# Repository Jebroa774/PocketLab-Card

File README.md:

# PocketLab Card V1

PocketLab Card V1 is an original, credit-card-outline ESP32-S3 field tool with
Wi-Fi/BLE control, NFC, LF RFID, Sub-GHz, infrared, removable storage and a
small local user interface. The hardware is designed around a four-layer PCB,
a single-cell LiPo supply and parts that can be assembled by JLCPCB or fitted by
hand where practical.

> [!NOTE]
> **Proudly vibe-coded.** The project grows through hands-on experimentation,
> rapid idea-driven iteration and AI-assisted engineering. Here, vibe coding
> does not mean blindly trusting generated output: the hardware remains an
> engineering prototype until its schematic, PCB, DRC/DFM results and physical
> measurements have been independently checked.

> [!WARNING]
> **Engineering prototype — not ready to order.** Placement and electrical
> connectivity are complete: the current routing checkpoint has 0 open
> connection items. It still has 1,164 DRC findings in the saved median run,
> so DRC/DFM cleanup, RF/LF tuning, sourcing review and prototype measurements
> remain required before fabrication.

## Current hardware

| Area | V1 implementation |
|---|---|
| Controller | ESP32-S3-WROOM-1-N8R2 with native USB, Wi-Fi and BLE |
| 13.56 MHz NFC | PN532 with a project-local 35 x 27 mm four-turn PCB antenna |
| 125 kHz LF RFID | HTRC110 front end with a removable, measurable and tuneable coil |
| Sub-GHz | E07-900MM10S/CC1101 module, tuneable pi network and inboard 868 MHz spring antenna |
| Infrared | Three independent high-power 940 nm emitters plus a 38 kHz receiver |
| Storage and security | microSD, ATECC608C secure element and physical PAIR button |
| User interface | Four RGB LEDs, UP/SELECT/DOWN controls and a firmware-configurable AUX button |
| Sensors | Optional 6-axis IMU, barometer, RTC, fuel gauge and board-temperature monitor |
| Power | USB-C, 1-cell LiPo input, charging/power path, regulated 3.3 V and switchable 5 V |
| Expansion | Protected 2.54 mm breakout matrix with eleven direct expansion GPIOs |

The **ESP32-S3 remains the controller for V1**. The newer ESP32-S31 is being
kept as a possible V2 candidate, but its preliminary hardware ecosystem,
larger WROOM module and immature availability do not justify restarting this
layout.

## Current PCB views

The following images were generated from the current KiCad routing checkpoint.
The hand-fitted IR bodies and spring antenna use approximate preview models;
footprints, courtyards and the PCB outline remain the mechanical references.

<table>
  <tr>
    <td align="center"><br><strong>Top</strong></td>
    <td align="center"><br><strong>Bottom</strong></td>
  </tr>
</table>

More layout and enclosure notes are available in the
[design overview](docs/design-overview/README.md).

## Mechanical target

- 85.60 x 53.98 mm credit-card outline with rounded corners
- Four-layer, nominal 1.2 mm FR-4 using the JLC04121H-7628 stack target
- 1 oz outer and 0.5 oz inner copper with ENIG finish
- Components on both sides; approximately 8–9 mm provisional assembled height
- Three inboard edge-facing IR emitters and an inboard spring-antenna pocket
- Compact unpopulated 6 x 5 matrix of 30 holes on 2.54 mm pitch
- Initial bring-up quantity: five assembled prototype boards

This is a credit-card-shaped instrument, not a wallet-thickness card. The final
height and enclosure clearances must be verified against received components.

## Engineering status

| Check | Current result |
|---|---:|
| Schematic symbols | 274 |
| Assigned footprints | 267 |
| Named logical nets | 181 |
| Physical PCB nets | 231 |
| ERC | 0 errors / 0 warnings |
| Placed footprints | 267 / 267 |
| Routed checkpoint | 2843 track segments / 575 vias / 23 zones |
| Remaining connection items | 0 |
| DRC findings (median of three runs) | 1164 |
| Footprint-library comparison findings | 5 |

Completed design work includes the full schematic, mechanical placement,
four-layer stack definition, native USB pair, local converter routes, RTC
crystal routes, the provisional Sub-GHz feed/pi network and the via-free
back-side LF RFID analog island. All logical connection items are now closed;
the active work is reducing the remaining clearance, hole-clearance, short,
crossing, solder-mask and board-edge DRC findings.

### Before the first PCB order

- Confirm the live JLCPCB stack and recalculate USB/Sub-GHz geometry.
- Review the completed LF/NFC and digital routing against the schematic.
- Finish DRC cleanup, ground stitching and plane review.
- Re-run final KiCad DRC/parity checks from a clean checkout.
- Review every footprint, BOM and placement entry against current supplier data.
- Reconfirm PN532 availability because the part is NRND, and qualify an
  alternative before any production revision.
- Inspect the JLCPCB DFM, BOM and CPL previews and obtain an independent review.
- Tune NFC, LF RFID and Sub-GHz on the assembled prototypes with suitable test
  equipment before treating any RF values as production-ready.

The detailed hand-off state is maintained in the
[work checkpoint](docs/work-checkpoint.md).

## Repository layout

```text
PocketLab-Card/
|-- docs/           Architecture, constraints, checkpoints and current renders
|-- hardware/       KiCad source, local libraries, reports and layout helpers
|-- firmware/       ESP32-S3 firmware source and board configuration
`-- manufacturing/  Fabrication/assembly generation tools and future releases
```

Open `hardware/PocketLab-Card.kicad_pro` in KiCad 10 for the complete project.
The tracked `hardware/PocketLab-Card.kicad_pcb` is the current routing-in-progress
board, not a fabrication release.

## Responsible use

RF, RFID/NFC and infrared functions are intended only for devices, systems,
frequencies, antennas, output levels and duty cycles the operator is legally
permitted to use. Prototype RF performance, electromagnetic compatibility and
regulatory compliance have not yet been verified.

The project is original and does not copy SGP branding, artwork, PCB layout or
firmware.

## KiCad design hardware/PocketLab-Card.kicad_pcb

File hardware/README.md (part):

# Hardware design source

## Functional blocks

| Logical block | Contents |
|---|---|
| 00_ROOT | Power domains, buses and hierarchical connections |
| 01_USB_POWER | USB-C, ESD, charger, battery, 3.3 V and 5 V conversion |
| 02_MCU | ESP32-S3-WROOM-1 module, boot/reset and native USB |
| 03_NFC | PN532, clock, matching/RX networks and four-turn PCB loop |
| 04_SUBGHZ | E07-900MM10S CC1101 module, tuneable pi network and inboard spring antenna |
| 05_LF_RFID_SD | HTRC110, removable 125 kHz coil, level shifting, ATECC608C, PAIR and microSD |
| 06_IR_UI | IR transmitter/receiver, RGB LEDs and buttons |
| 07_SENSORS_IO | IMU, barometer, RTC, fuel gauge, U9/U18 and headers |

KiCad 10 is installed locally. `PocketLab-Card.kicad_pro` is the project entry
point and the PCB scaffold contains the exact credit-card outline. The current
generated schematic comprises 267 symbols and 176 named logical nets; the
OLED-free PCB candidate contains 260 footprints. `reports/erc-nooled-aux.rpt` reports zero
errors and zero warnings.

The schematic and its machine-readable net description are reproducible with
KiCad's bundled Python:

```powershell
& "$env:LOCALAPPDATA\Programs\KiCad\10.0\bin\python.exe" scripts/generate_schematic.py PocketLab-Card.kicad_sch --design-json design-netlist.json
```

The project-local footprint library includes the manufacturer-derived special
packages and `NFC_Loop_35x27mm_4T_TUNE`. The latter is a four-turn, 0.50/0.50
mm preliminary loop with a 35 x 27 mm copper envelope and a full 36 x 29 mm
all-copper-layer keep-out. Its matching is intentionally not a release value:
measure and tune the populated prototype with the final stack-up, enclosure and
battery using a VNA or suitable NFC fixture.

The tracked `PocketLab-Card.kicad_pcb` remains the authoritative design source.
`PocketLab-Card-routing-working.kicad_pcb` is the explicitly named active routing
checkpoint and is kept only so the verified zero-open state can be resumed without
promoting it prematurely. Other generated placement, plane, autorouter and
routing-progress boards are deliberately not versioned because the scripts below
recreate them from the schematic, mechanical template and current rules.

The current PCB contains the guarded digital autorouter fanout plus reviewed local U6/L6,
U7/L7, converter input/output, U7-feedback, RTC-crystal and complete native USB
data routes; L2 remains the uninterrupted ground plane and L3 retains the
power polygons plus explicitly reviewed low-speed signal crossings. R201/R202 are vertical side-by-side 0805
parts, the MCU-side pair stays via-free, and a staggered five-via bridge joins
J1's alternating A/B data pads. U16 is 0.55 mm farther inboard; front-side
0805 R102 now has its J1-B5 pull-down and local ground return routed. The CC2
protection branch to U16 pin 6 is also complete using two ordinary 0.50/0.30-mm
through vias and outer-layer tracks only. SW3/SW7/SW4 are compact, adjacent UP/OK/DOWN
controls; SELECT uses U9/P07 and the BMP390 remains available by I2C polling.
VSYS is now complete through the charger/converter island; an 0805 zero-ohm
SPI_MOSI crossover preserves the plane-only inner layers. Both J1 VBUS contacts
also reach F1 through reviewed local neckdowns and 0.50/0.60-mm B.Cu copper.
The provisional 868-MHz feed now runs through the correctly oriented pi network
and makes its sole signal-layer transition before the spring pocket; its F.Cu
section remains on the narrow PCB bridge outside the notch. The present
checkpoint has 1889 track segments, 343 vias and 23 zones. Both `+5V_RAW` and
`+5V_AUX` are complete on narrow L3 corridors, the requested 36 dense-plane
clusters are closed, and the reviewed U2.3 GND escape is routed. R405 is
oriented with pad 1 toward U3 and pad 2 toward the antenna. The microSD socket
is now 0.175 mm farther inboard, eliminating its ten copper-to-edge findings.
J5.25 now reaches the complete U25/R732 `SPI_SCK_HDR` protection tree through
a reviewed short L3 crossing. J5.23 reaches U24.1 on `I2C_SDA_HDR`; its separate
R730 branch remains in the ratsnest. A single reviewed `+5V_RAW` stitch via
keeps the power polygon connected around the SCK clearance slot, and L2 remains
ground-only.
The short PN532 `/NFC_TX2_F` matching branch from L302.2 to C309.1 is now
routed via-free on F.Cu through the reviewed 0.25-mm local corridor.
The microSD controller-side `/SD_CS_DEV` leg now reaches J2.2 through one local
via; the adjacent U19.2 GND escape was shifted toward the card edge without
changing its reviewed plane via.
The ESP32 `/SPI_MOSI` pad U1.19 now reaches the existing U21/R129 shared-bus
trunk through eight locked outer-layer segments and one 0.45/0.20-mm via.
R511.1 now joins that same trunk through six locked 0.15-mm L3 segments, one
short F.Cu escape and one 0.45/0.20-mm via. The route preserves the continuous
L2 ground plane and the connectivity of both protected L3 5-V polygons.
The USB-C `/USB_CC1` receptacle pad J1.A5 now reaches its back-side 5.1-kohm
pull-down R101 through one outer-layer transition. U16.4 now joins that same
group through nine locked 0.20-mm F.Cu segments, so the complete CC1 detection
and ESD branch is connected without another via.
The UP-button `/USER_BUTTON_A_N` contact SW3.1 now reaches pull-up R608.1
through one short reviewed L3 crossing and two 0.45/0.20-mm vias; U18.11
remains the explicit second group on that net.
The back-side `/CELL_POS` monitor input U8.3 now reaches local capacitor C120.1
through four short, via-free 0.15-mm B.Cu segments.
The back-side `/CELL_POS` sense input R104.1 now joins the charger/battery
branch through three locked 0.20-mm B.Cu segments, one 0.45/0.20-mm tented via
and five locked 0.20-mm F.Cu segments. The route uses the narrow reviewed gap
between C101 and C117 without cutting any inner-layer power polygon.
The protected `/GPIO43` output R718.2 now reaches expansion-header pad J5.11
through three locked 0.15-mm L3 segments and one 0.45/0.20-mm tented via.
The protected `/SPI_MISO_HDR` branch now joins resistor R734.2 to J5 ESD-array
channel U25.1 through eleven locked 0.15-mm segments, two 0.45/0.20-mm tented
vias and a reviewed L3 corridor; the dedicated L2 GND plane remains untouched.
The PN532 `/NFC_TX1` driver pad U2.4 now reaches matching inductor L301.1
through two short F.Cu escapes, three locked 0.20-mm L3 segments and two
0.45/0.20-mm tented vias. Small reviewed jogs in the neighboring LF clock/data
fanouts preserve their connectivity and keep the dedicated L2 GND plane clean.
The active routing checkpoint contains 2843 track segments, 575 ordinary through
vias and 23 zones. Three fresh KiCad DRC runs report zero open connections and
totals between 1162 and 1166 remaining violations (median 1164). The latest cleanup
reroutes EX4, EX5, CHG_TS_FIXED, GPIO8_MCU and SD_DETECT_N, reassigns CHARGER_CHG_N,
and rehomes the AUX5_FAULT_N and BAT_SENSE vias while preserving connectivity.
The earlier cleanup merges one
redundant same-net NFC_OSCOUT via pair, rehomes two crowded GND vias and eliminates
the remaining hole-to-hole findings (three to zero). A CHG_TS L3 detour reduces the
copper-to-edge findings from five to four. Small conventional-through-via rehomes
also improve CHG_ITERM, NFC_DVDD and IR_TX while preserving the long IR_TX inner
trace; no blind or microvias were introduced. The earlier cleanup removes the PWR
copper sliver and both GPIO8-to-rounded-corner edge findings without introducing a
keepout violation. It also merges redundant BAT_SENSE, NFC_SVDD and SD_SCK via
pairs and makes the local USB_CONN_P join via-free.
The remaining violations still require grouped cleanup; the board is therefore not
an order-ready fabrication release.
The matching machine-readable report is `reports/PocketLab-Card-drc.json`.

The latest PN532 cleanup connects U2.5/U2.8 with a short via-free DVDD escape
and replaces the old west-side U2.3 GND detour with a direct exposed-pad
connection. `scripts/route_nfc_dvdd_escape.py` reproduces that reviewed stage.

The LF_RFID_EN branch now reaches U22.1 through a reviewed L3 signal corridor.
The change reuses the former redundant +3V3 via site, reconnects R109 to the
retained +3V3 fanout and leaves L2 as a ground-only plane.
`scripts/route_lf_enable.py` reproduces and connectivity-checks this stage.

The dense U8/U11 sensor corridor is also reworked. U8 SCL reaches U1.6 through
two standard 0.45/0.20-mm through-vias and a short L3 crossing, while U8 SDA
reaches U11.4 directly on B.Cu. `FG_ALERT_N` and `SPI_MOSI` were rerouted
around the corridor, the local U11 ground branches were restored, and L2
remains ground-only. `scripts/route_i2c_sensor_corridor.py` reproduces and
connectivity-checks all six affected endpoint pairs.

The reproducible routing helpers are:

```powershell
# Regenerate the placement and inner-plane staging boards
& "$env:LOCALAPPDATA\Programs\KiCad\10.0\bin\python.exe" scripts/build_pcb.py
& "$env:LOCALAPPDATA\Programs\KiCad\10.0\bin\python.exe" scripts/add_planes.py

# Export the full routing DSN
& "$env:LOCALAPPDATA\Programs\KiCad\10.0\bin\python.exe" scripts/route_pcb.py --export-only --force

# After a reviewed FreeRouting import, apply the local critical-route checkpoint
& "$env:LOCALAPPDATA\Programs\KiCad\10.0\bin\python.exe" scripts/route_critical.py --force

# Reproduce the reviewed LF_RFID_EN endpoint stage on a candidate board
& "$env:LOCALAPPDATA\Programs\KiCad\10.0\bin\python.exe" scripts/route_lf_enable.py --input PocketLab-Card.kicad_pcb --output PocketLab-Card-lf-enable-candidate.kicad_pcb --force

# Reproduce the reviewed U8/U11 I2C sensor corridor on a candidate board
& "$env:LOCALAPPDATA\Programs\KiCad\10.0\bin\python.exe" scripts/route_i2c_sensor_corridor.py --input PocketLab-Card.kicad_pcb --output PocketLab-Card-i2c-sensor-candidate.kicad_pcb --force

# Reproduce the reviewed via-free PN532 TX2 matching branch
& "$env:LOCALAPPDATA\Programs\KiCad\10.0\bin\python.exe" scripts/route_nfc_tx2_matching.py --input PocketLab-Card.kicad_pcb --output PocketLab-Card-nfc-tx2-matching-candidate.kicad_pcb --force

# Reproduce the reviewed microSD CS socket leg and local U19 GND rehome
& "$env:LOCALAPPDATA\Programs\KiCad\10.0\bin\python.exe" scripts/route_sd_cs_socket.py --input PocketLab-Card.kicad_pcb --output PocketLab-Card-sd-cs-candidate.kicad_pcb --force

# Reproduce the reviewed ESP32-to-shared-trunk SPI-MOSI branch
& "$env:LOCALAPPDATA\Programs\KiCad\10.0\bin\python.exe" scripts/route_spi_mosi_mcu.py --input PocketLab-Card.kicad_pcb --output PocketLab-Card-spi-mosi-mcu-candidate.kicad_pcb --force

# Reproduce the reviewed shared-trunk-to-R511 SPI-MOSI branch
& "$env:LOCALAPPDATA\Programs\KiCad\10.0\bin\python.exe" scripts/route_spi_mosi_sd_resistor.py --input PocketLab-Card.kicad_pcb --output PocketLab-Card-spi-mosi-r511-candidate.kicad_pcb --force

# Reproduce the reviewed U8-to-C120 CELL_POS monitor branch
& "$env:LOCALAPPDATA\Programs\KiCad\10.0\bin\python.exe" scripts/route_cell_pos_monitor.py --input PocketLab-Card.kicad_pcb --output PocketLab-Card-cell-pos-monitor-candidate.kicad_pcb --force

# Reproduce the reviewed R104-to-main CELL_POS sense branch
& "$env:LOCALAPPDATA\Programs\KiCad\10.0\bin\python.exe" scripts/route_cell_pos_sense_branch.py --input PocketLab-Card.kicad_pcb --output PocketLab-Card-cell-pos-sense-candidate.kicad_pcb --force

# Reproduce the reviewed protected GPIO43-to-header branch
& "$env:LOCALAPPDATA\Programs\KiCad\10.0\bin\python.exe" scripts/route_gpio43_header.py --input PocketLab-Card.kicad_pcb --output PocketLab-Card-gpio43-header-candidate.kicad_pcb --force

# Reproduce the reviewed protected SPI-MISO resistor-to-ESD branch
& "$env:LOCALAPPDATA\Programs\KiCad\10.0\bin\python.exe" scripts/route_spi_miso_header_esd.py --input PocketLab-Card.kicad_pcb --output PocketLab-Card-spi-miso-header-esd-candidate.kicad_pcb --force

# Reproduce the reviewed PN532 TX1 driver-to-inductor branch
& "$env:LOCALAPPDATA\Programs\KiCad\10.0\bin\python.exe" scripts/route_nfc_tx1_driver.py --input PocketLab-Card.kicad_pcb --output PocketLab-Card-nfc-tx1-candidate.kicad_pcb --force

# Reproduce the reviewed USB-C CC1 receptacle-to-pull-down path
& "$env:LOCALAPPDATA\Programs\KiCad\10.0\bin\python.exe" scripts/route_usb_cc1_resistor.py --input PocketLab-Card.kicad_pcb --output PocketLab-Card-usb-cc1-resistor-candidate.kicad_pcb --force

# Reproduce the reviewed USB-C CC1 receptacle-to-U16 ESD branch
& "$env:LOCALAPPDATA\Programs\KiCad\10.0\bin\python.exe" scripts/route_usb_cc1_esd_branch.py --input PocketLab-Card.kicad_pcb --output PocketLab-Card-usb-cc1-esd-candidate.kicad_pcb --force

# Reproduce the reviewed UP-button contact-to-pull-up path
& "$env:LOCALAPPDATA\Programs\KiCad\10.0\bin\python.exe" scripts/route_user_button_a_pullup.py --input PocketLab-Card.kicad_pcb --output PocketLab-Card-user-button-a-candidate.kicad_pcb --force

# Reproduce the reviewed J5 SDA/SCK protection checkpoint as a candidate chain
& "$env:LOCALAPPDATA\Programs\KiCad\10.0\bin\python.exe" scripts/route_header_bus_protection.py --input PocketLab-Card.kicad_pcb --output PocketLab-Card-header-protection-candidate.kicad_pcb --force
& "$env:LOCALAPPDATA\Programs\KiCad\10.0\bin\python.exe" scripts/rehome_header_neck_fanouts.py --input PocketLab-Card-header-protection-candidate.kicad_pcb --output PocketLab-Card-header-neck-candidate.kicad_pcb --force
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
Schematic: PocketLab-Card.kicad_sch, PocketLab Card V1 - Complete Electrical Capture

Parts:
A1: T3-868M SPRING ANTENNA; T3-868M_Edge_Solder; MPN T3-868M; LCSC C381193
AE1: PCB NFC LOOP - TUNE ON V1; NFC_Loop_35x27mm_4T_TUNE
C101: 4.7nF 1kV; C_0805_2012Metric; MPN C0805C472KDRAC7800; LCSC C5565742
C102, C106, C107, C118, C120, C121, C122, C203, C301, C304, C305, C401, C510, C601, C603, C604, C605, C606, C701, C702, C703, C704, C705, C706, C707: 100nF; C_0402_1005Metric; MPN CL05B104KO5NNNC; LCSC C1525
C103, C105: 4.7uF 10V; C_0603_1608Metric; MPN CL10A475KO8NNNC; LCSC C19666
C104: 22uF 10V; C_0805_2012Metric; MPN TCC0805X5R226K100FT; LCSC C380336
C108, C114, C117, C119: 10uF; C_0805_2012Metric; MPN CL21A106KAYNNNE; LCSC C15850
C109: 10uF DNP - populate only after VSYS stability test; C_0805_2012Metric; MPN CL21A106KAYNNNE; LCSC C15850; not fitted
C110, C111, C112, C115, C116: 22uF; C_0805_2012Metric; MPN TCC0805X5R226K100FT; LCSC C380336
C113, C308, C309: 220pF C0G; C_0603_1608Metric; MPN CL10C221JB8NNNC; LCSC C27675
C123, C124: 10uF 25V X5R HF; C_0805_2012Metric; MPN CL21A106KAYNNNE; LCSC C15850
C201: 1uF; C_0402_1005Metric; MPN CL05A105KA5NQNC; LCSC C52923
C202, C511: 10uF; C_0603_1608Metric; MPN CL10A106KP8NNNC; LCSC C19702
C302: 100nF AVDD; C_0402_1005Metric; MPN CL05B104KO5NNNC; LCSC C1525
C303: 4.7uF VBAT bulk; C_0603_1608Metric; MPN CL10A475KO8NNNC; LCSC C19666
C306, C307: 22pF C0G; C_0603_1608Metric; MPN CL10C220JB8NNNC; LCSC C1653
C310, C311, C312: DNP MATCH; C_0603_1608Metric; not fitted
C313: 10uF DVDD bulk; C_0603_1608Metric; MPN CL10A106KP8NNNC; LCSC C19702
C314: 100nF TVDD; C_0402_1005Metric; MPN CL05B104KO5NNNC; LCSC C1525
C315: 4.7uF TVDD bulk; C_0603_1608Metric; MPN CL10A475KO8NNNC; LCSC C19666
C316: 100nF PVDD; C_0402_1005Metric; MPN CL05B104KO5NNNC; LCSC C1525
C317: 100nF VBAT; C_0402_1005Metric; MPN CL05B104KO5NNNC; LCSC C1525
C318: 1nF C0G RX COUPLING; C_0603_1608Metric; MPN CL10C102JB8NNNC; LCSC C163508
C402, C602: 4.7uF; C_0603_1608Metric; MPN CL10A475KO8NNNC; LCSC C19666
C403, C404: DNP SUBGHZ MATCH; C_0603_1608Metric; not fitted
C501: 100nF HTRC supply; C_0402_1005Metric; MPN CL05B104KO5NNNC; LCSC C1525
C502: 10uF HTRC pulse reservoir; C_0805_2012Metric; MPN CL21A106KAYNNNE; LCSC C15850
C503: 100nF CEXT; C_0402_1005Metric; MPN CL05B104KO5NNNC; LCSC C1525
C504: 100nF QGND; C_0402_1005Metric; MPN CL05B104KO5NNNC; LCSC C1525
C505: 100nF C0G COIL ISOLATION; C_1206_3216Metric; MPN 1206CG104J500NT; LCSC C46348
C506: 3.9nF C0G LF RESONANCE; C_0805_2012Metric; MPN CL21C392JBFNNNE; LCSC C307553
C507: 100pF C0G DNP LF TUNE; C_0603_1608Metric; MPN CL10C101JB8NNNC; LCSC C14858; not fitted
C508: 220pF C0G DNP LF TUNE; C_0603_1608Metric; MPN CL10C221JB8NNNC; LCSC C27675; not fitted
C509: 10pF C0G DNP RX EMI; C_0603_1608Metric; MPN CL10C100JB8NNNC; LCSC C1634; not fitted
C512: 47uF 6.3V LOW-ESR; C_1206_3216Metric; MPN CC1206MKX5R5BB476; LCSC C110047
C513: 100nF OSC supply; C_0402_1005Metric; MPN CL05B104KO5NNNC; LCSC C1525
C515: 100nF LV-AT supply; C_0402_1005Metric; MPN CL05B104KO5NNNC; LCSC C1525
C516: 100nF LVC supply; C_0402_1005Metric; MPN CL05B104KO5NNNC; LCSC C1525
C517: 100nF secure element; C_0402_1005Metric; MPN CL05B104KO5NNNC; LCSC C1525
C607, C617: 22uF 10V X5R IR BUFFER; C_1206_3216Metric; MPN TCC1206X5R226K100HT; LCSC C7393980
C608: 100nF IR HF; C_0402_1005Metric; MPN CL05B104KO5NNNC; LCSC C1525
C609: 100nF X7R; C_0402_1005Metric; MPN CL05B104KO5NNNC; LCSC C1525
D1, D2, D3: VSMY14940 940nm side-view; LED_Vishay_VSMY14940_SideView; MPN VSMY14940; LCSC C511069
D101: SMF5.0A; D_SOD-123F; MPN SMF5.0A; LCSC C151296
F1: Littelfuse 1206L075/13.2; Fuse_1206_3216Metric; MPN 1206L075/13.2WR; LCSC C207036
J1: USB-C DATA/POWER; USB_C_Receptacle_HRO_TYPE-C-31-M-12; MPN TYPE-C-31-M-12; LCSC C165948
J2: microSD; microSD_HC_Molex_104031-0811; MPN 104031-0811; LCSC C585350
J3: EXTERNAL 400uH LF COIL; PinHeader_1x02_P2.54mm_Vertical
J4: PROTECTED 1S LiPo 3.7V; JST_PH_S2B-PH-SM4-TB_1x02-1MP_P2.00mm_Horizontal; MPN S2B-PH-SM4-TB(LF)(SN); LCSC C295747
J5: 30-PIN 2.54mm DUPONT GRID; Dupont_Grid_6x5_P2.54mm
L6: 1.5uH 5.2A SMHT4020; ShunXiangNuo_SMHT4020; MPN SMHT4020-1R5MT; LCSC C46469583
L7: 1uH 4.15A SLW4030S; Sunltech_SLW4030S; MPN SLW4030S1R0NST; LCSC C206354
L301, L302: 560nH C0G/Q; L_0805_2012Metric; MPN FHW0805UFR56JST; LCSC C304279
LED1, LED2, LED3, LED4: WS2812B-2020; LED_WS2812B-2020_PLCC4_2.0x2.0mm; MPN WS2812B-2020; LCSC C965555
Q1: AO3400A IR DRIVER; SOT-23; MPN AO3400A; LCSC C20917
Q2: CSD16406Q3 DISCHARGE; CSD16406Q3_VSON-8_3.3x3.3mm_P0.65mm_JLC; MPN CSD16406Q3; LCSC C2861720
Q3: CSD16406Q3 CHARGE; CSD16406Q3_VSON-8_3.3x3.3mm_P0.65mm_JLC; MPN CSD16406Q3; LCSC C2861720
R101, R102: 5.1k 1%; R_0402_1005Metric; MPN 0402WGF5101TCE; LCSC C25905
R103: 1M; R_0402_1005Metric; MPN 0402WGF1004TCE; LCSC C26083
R104: 330R; R_0402_1005Metric; MPN 0402WGF3300TCE; LCSC C25104
R105: 2.2k; R_0805_2012Metric; MPN 0805W8F2201T5E; LCSC C17520
R106, R107: 5.1M; R_0402_1005Metric; MPN 0402WGF5104TCE; LCSC C270595
R108: 10k TS fixed; R_0805_2012Metric; MPN 0805W8F1002T5E; LCSC C17414
R109, R110, R115, R122, R124, R126, R127, R128, R603: 100k; R_0402_1005Metric; MPN 0402WGF1003TCE; LCSC C25741
R111: 3.48k 1%; R_0402_1005Metric; MPN 0402WGF3481TCE; LCSC C22065
R112: 3.01k 1%; R_0402_1005Metric; MPN 0402WGF3011TCE; LCSC C25889
R113: 1.78k 1%; R_0402_1005Metric; MPN 0402WGF1781TCE; LCSC C113478
R114: 68.1k 1%; R_0402_1005Metric; MPN 0402WGF6812TCE; LCSC C11537
R116, R125, R203, R204, R301, R519, R607, R608, R609, R703: 10k; R_0402_1005Metric; MPN 0402WGF1002TCE; LCSC C25744
R117: 470k 1%; R_0402_1005Metric; MPN 0402WGF4703TCE; LCSC C25790
R118: 150k 1%; R_0402_1005Metric; MPN 0402WGF1503TCE; LCSC C25755
R119: 10k; R_0805_2012Metric; MPN 0805W8F1002T5E; LCSC C17414
R120: 732k 1%; R_0402_1005Metric; MPN 0402WGF7323TCE; LCSC C27016
R121: 100k 1%; R_0402_1005Metric; MPN 0402WGF1003TCE; LCSC C25741
R123: 60.4k 1%; R_0402_1005Metric; MPN 0402WGF6042TCE; LCSC C25911
R129: 0R SPI CROSSOVER; R_0805_2012Metric; MPN 0805W8F0000T5E; LCSC C17477
R201, R202: 22R; R_0805_2012Metric; MPN 0805W8F220JT5E; LCSC C17561
R302: 10k RESET default asserted; R_0402_1005Metric; MPN 0402WGF1002TCE; LCSC C25744
R303, R304: 0R MATCH; R_0603_1608Metric; MPN 0603WAF0000T5E; LCSC C21189
R305: 2.7k RX TAP; R_0603_1608Metric; MPN 0603WAF2701T5E; LCSC C13167
R306: 1k VMID BIAS; R_0603_1608Metric; MPN 0603WAF1001T5E; LCSC C21190
R401, R402, R403, R404, R510, R511, R512, R513: 22R; R_0402_1005Metric; MPN 0402WGF220JTCE; LCSC C25092
R405: 0R SUBGHZ MATCH; R_0603_1608Metric; MPN 0603WAF0000T5E; LCSC C21189
R406: 100k CS SAFE-HIGH; R_0402_1005Metric; MPN 0402WGF1003TCE; LCSC C25741
R501: 100R QOD discharge; R_0402_1005Metric; MPN 0402WGF1000TCE; LCSC C25076
R502: 47R 0.5W ANTENNA CURRENT LIMIT; R_1210_3225Metric; MPN 1210W2F470JT5E; LCSC C474213
R503: 1k LF EMI RETURN; R_0402_1005Metric; MPN 0402WGF1001TCE; LCSC C11702
R504: 150k 1% RX DIVIDER; R_0402_1005Metric; MPN 0402WGF1503TCE; LCSC C25755
R506: 100k SAFE-OFF; R_0402_1005Metric; MPN 0402WGF1003TCE; LCSC C25741
R509: 10k PAIR pull-up; R_0402_1005Metric; MPN 0402WGF1002TCE; LCSC C25744
R514, R515, R516, R517, R518: 47k; R_0402_1005Metric; MPN 0402WGF4702TCE; LCSC C25792
R601, R610, R611: 68R 0.25W anti-surge; R_0603_1608Metric; MPN AS03W4J0680T5E; LCSC C966162
R602, R604, R710, R711, R712, R713, R715, R716, R717, R718, R719, R720, R721, R730, R731, R732, R733, R734: 100R; R_0402_1005Metric; MPN 0402WGF1000TCE; LCSC C25076
R605: 68R; R_0402_1005Metric; MPN 0402WGF680JTCE; LCSC C25131
R606: 100R PAIR GPIO PROTECTION; R_0402_1005Metric; MPN 0402WGF1000TCE; LCSC C25076
R701: 3.3k; R_0805_2012Metric; MPN 0805W8F3301T5E; LCSC C26010
R702: 3.3k; R_0402_1005Metric; MPN 0402WGF3301TCE; LCSC C25890
R714: 100R BOARD TEMP PROBE; R_0402_1005Metric; MPN 0402WGF1000TCE; LCSC C25076
R722, R723, R724, R725, R726, R727, R728, R729: 220R EXPANSION PROTECTION; R_0402_1005Metric; MPN 0402WGF2200TCE; LCSC C25091
R735: 100k EN pull-down; R_0805_2012Metric; MPN 0805W8F1003T5E; LCSC C149504
R736: 10k 1% BOARD TEMP BIAS; R_0402_1005Metric; MPN 0402WGF1002TCE; LCSC C25744
RT701: 10k NTC B3950 1%; R_0603_1608Metric; MPN KNTC0603/10KF3950; LCSC C2892547
SJ1: TS FIXED / CUT FOR EXT NTC; SolderJumper-2_P1.3mm_Bridged_RoundedPad1.0x1.5mm
SW1: RESET; SW_HYP_1TS015A_3.0x2.0mm; MPN 1TS015A-1600-0600-CT; LCSC C256104
SW2: BOOT; SW_HYP_1TS015A_3.0x2.0mm; MPN 1TS015A-1600-0600-CT; LCSC C256104
SW3: UP; SW_HYP_1TS015A_3.0x2.0mm; MPN 1TS015A-1600-0600-CT; LCSC C256104
SW4: DOWN; SW_HYP_1TS015A_3.0x2.0mm; MPN 1TS015A-1600-0600-CT; LCSC C256104
SW5: MAIN POWER OFF / ON; SW_SPDT_Shouhan_MSK12C02; MPN MSK12C02; LCSC C431540
SW6: PAIR; SW_HYP_1TS015A_3.0x2.0mm; MPN 1TS015A-1600-0600-CT; LCSC C256104
SW7: SELECT; SW_HYP_1TS015A_3.0x2.0mm; MPN 1TS015A-1600-0600-CT; LCSC C256104
SW8: AUX CONFIG; SW_SPST_CK_KXT3; MPN KXT311LHS
TP101: BATTERY CELL_POS; TestPoint_Pad_D1.0mm
TP102: BATTERY CELL_NEG; TestPoint_Pad_D1.0mm
TP103: BATTERY BAT_FET_MID; TestPoint_Pad_D1.0mm
TP104: BATTERY GND; TestPoint_Pad_D1.0mm
TP105: POWER VBUS_USB; TestPoint_Pad_D1.0mm
TP106: POWER VBUS_FUSED; TestPoint_Pad_D1.0mm
TP107: POWER VSYS; TestPoint_Pad_D1.0mm
TP108: POWER +3V3; TestPoint_Pad_D1.0mm
TP109: POWER +5V_RAW; TestPoint_Pad_D1.0mm
TP110: POWER +5V_AUX; TestPoint_Pad_D1.0mm
TP201: JTAG_STRAP_TP; TestPoint_Pad_D1.0mm
TP202: STRAP_BOOT_TP; TestPoint_Pad_D1.0mm
TP203: STRAP_VDD_SPI_TP; TestPoint_Pad_D1.0mm
TP301: NFC_LOADMOD TEST; TestPoint_Pad_D1.0mm
TP502: LF ANTENNA TAP - HIGH VOLTAGE; TestPoint_Pad_D1.0mm
U1: ESP32-S3-WROOM-1-N8R2; ESP32-S3-WROOM-1_PhysicalCourtyard; MPN ESP32-S3-WROOM-1-N8R2; LCSC C2913204
U2: PN5321A3HN/C106; HVQFN-40-1EP_6x6mm_P0.5mm_EP4.1x4.1mm; MPN PN5321A3HN/C106; LCSC C880904
U3: E07-900MM10S 855-925MHz; E07-900MM10S; MPN E07-900MM10S; LCSC C5844212
U4: HTRC11001T/03EE,11 125kHz; SO-14_3.9x8.65mm_P1.27mm; MPN HTRC11001T/03EE,11; LCSC C501317
U5: BQ24074RGTR; VQFN-16-1EP_3x3mm_P0.5mm_EP1.6x1.6mm_ThermalVias; MPN BQ24074RGTR; LCSC C54313
U6: TPS63070RNMR 3V3; TPS63070_RNM0015A; MPN TPS63070RNMR; LCSC C109322
U7: TPS61023DRLR 5V BOOST; SOT-563; MPN TPS61023DRLR; LCSC C919459
U8: MAX17048G+T10; TDFN-8-1EP_2x2mm_P0.5mm_EP0.8x1.2mm; MPN MAX17048G+T10; LCSC C2682616
U9: TCA9535PWR; TSSOP-24_4.4x7.8mm_P0.65mm; MPN TCA9535PWR; LCSC C130204
U10: BMI270 (FULL OPTION); Bosch_LGA-14_3x2.5mm_P0.5mm; MPN BMI270; LCSC C2836813
U11: BMP390 (FULL OPTION); BMP390_LGA-10_2x2mm; MPN BMP390; LCSC C5124834
U12: PCF8563T; SOIC-8_3.9x4.9mm_P1.27mm; MPN PCF8563T/5,518; LCSC C7440
U13: TSOP75338WTR 38kHz; TSOP75338WTR_HeimdallW_SideView; MPN TSOP75338WTR; LCSC C7365598
U14: BQ29700DSE; WSON-6_1.5x1.5mm_P0.5mm; MPN BQ29700DSER; LCSC C183096
U15: TPS2553DBVR 500mA LIMIT; SOT-23-6; MPN TPS2553DBVR; LCSC C55266
U16: USBLC6-4SC6Y; SOT-23-6; MPN USBLC6-4SC6Y; LCSC C435848
U17: TPS22919DCKR LF 5V LOAD SWITCH; SOT-363_SC-70-6; MPN TPS22919DCKR; LCSC C2149796
U18: TCA9534PWR INTERNAL CONTROL; TSSOP-16_4.4x5mm_P0.65mm; MPN TCA9534PWR; LCSC C783615
U19: SRV05-4MR6T1G SD ESD; SOT-23-6; MPN SRV05-4MR6T1G; LCSC C604719
U20: SN74AHCT1G126DBVR RGB LEVEL SHIFT; SOT-23-5; MPN SN74AHCT1G126DBVR; LCSC C163712
U21: SN74LV125ATPWR LF/SPI 3V3-TO-5V IOFF; TSSOP-14_4.4x5mm_P0.65mm; MPN SN74LV125ATPWR; LCSC C2675655
U22: SN74LVC1G126DBVR LF 5V-TO-3V3 TRI-STATE; SOT-23-5; MPN SN74LVC1G126DBVR; LCSC C7834
U23: ATECC608C-SSHDA-T; SOIC-8_3.9x4.9mm_P1.27mm; MPN ATECC608C-SSHDA-T; LCSC C28975195
U24: SRV05-4MR6T1G J5 BUS ESD; SOT-23-6; MPN SRV05-4MR6T1G; LCSC C604719
U25: SRV05-4MR6T1G J5 SPI ESD; SOT-23-6; MPN SRV05-4MR6T1G; LCSC C604719
Y301: 27.12MHz crystal (pins 2/4 shield); Crystal_SMD_3225-4Pin_3.2x2.5mm; MPN XXDBBCNANF-27.12M; LCSC C124317
Y501: 4MHz 5V CMOS OSCILLATOR; Oscillator_SMD_EuroQuartz_XO32-4Pin_3.2x2.5mm_RotB; MPN OH2EL89CFI-111YLC-4M; LCSC C42448900
Y701: 32.768kHz CL=7pF; Crystal_SMD_3215-2Pin_3.2x1.5mm; MPN ABS07-32.768KHZ-7-T; LCSC C276424

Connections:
/+3V3: C110.1, C111.1, C112.1, C124.1, C202.1, C203.1, C303.1, C316.1, C317.1, C401.1, C402.1, C510.1, C511.1, C512.1, C516.1, C517.1, C701.1, C702.1, C703.1, C704.1, C705.1, C706.1, C707.1, J2.4 (VDD), J5.1, R109.2, R110.2, R117.1, R119.2, R124.2, R125.2, R203.2, R204.2, R406.2, R509.2, R514.2, R515.2, R516.2, R517.2, R518.2, R519.2, R604.1, R607.2, R608.2, R609.2, R701.2, R702.2, R703.2, R736.1, TP108.1, U1.2 (3V3), U2.23 (PVDD), U2.40 (VBAT), U3.1, U6.7, U6.8, U9.24 (VCC), U10.5, U10.8, U10.12, U11.1, U11.6, U11.10, U12.8 (VDD), U18.1 (A0), U18.16 (VDD), U19.5 (VP), U22.5 (VCC), U23.8 (VCC), U24.5 (VP), U25.5 (VP); also elsewhere on the board
/+5V_AUX: C118.1, C119.1, J5.29, TP110.1, U15.6
/+5V_RAW: C113.1, C115.1, C116.1, C117.1, C603.1, C604.1, C605.1, C606.1, C607.1, C608.1, C609.1, C617.1, LED1.1 (VDD), LED2.1 (VDD), LED3.1 (VDD), LED4.1 (VDD), R120.1, R601.1, R610.1, R611.1, TP109.1, U7.6, U15.1, U17.1, U20.5 (VCC)
/AUX5_EN: R127.1, U15.3, U18.6 (P2)
/AUX5_FAULT_N: R124.1, U9.7 (P03), U15.4
/BAT_COUT: Q3.4, R107.1, U14.2 (Cout)
/BAT_DOUT: Q2.4, R106.1, U14.3 (Dout)
/BAT_FET_MID: Q2.5, Q3.5, TP103.1
/BAT_SENSE: C102.1, R104.2, U14.5 (BAT)
/BAT_VMINUS: R105.1, U14.6 (V-)
/BMI_INT1: U9.9 (P05), U10.4
/BMI_INT2: U9.10 (P06), U10.9
/BOARD_TEMP_ADC: R714.1, R736.2, RT701.1, U1.17 (IO9)
/BOARD_TEMP_HDR: J5.7, R714.2
/BOOST5_EN: R122.1, U7.2, U18.10 (P5), U20.1
/BOOT_N: R204.1, SW2.1, U1.27 (IO0)
/BQ_EN1: R115.1, U5.6 (EN1), U18.4 (P0)
/BQ_EN2: R128.1, U5.5 (EN2)
/CELL_NEG: C102.2, J4.2, Q2.1, Q2.2, Q2.3, R106.2, TP102.1, U14.4 (VSS)
/CELL_POS: C104.1, C120.1, C121.1, J4.1, R104.1, TP101.1, U5.2 (BAT), U5.3 (BAT), U8.3
/CHARGER_CHG_N: R110.1, U5.9 (~CHG), U9.5 (P01)
/CHARGER_PGOOD_N: R109.1, U5.7 (~PGOOD), U9.6 (P02)
/CHG_DISABLE: R126.1, U5.4 (~CE), U18.5 (P1)
/CHG_ILIM: R111.1, U5.12 (ILIM)
/CHG_ISET: R113.1, U5.16 (ISET)
/CHG_ITERM: R112.1, U5.15 (ITERM)
/CHG_TMR: R114.1, U5.14 (TMR)
/CHG_TS: J5.28, SJ1.1 (A), U5.1 (TS)
/CHG_TS_FIXED: R108.1, SJ1.2 (B)
/ESP_EN: C201.1, R203.1, SW1.1, U1.3 (EN); also elsewhere on the board
/EX0: J5.15, R722.2
/EX0_INT: R722.1, U9.13 (P10)
/EX1: J5.16, R723.2
/EX1_INT: R723.1, U9.14 (P11)
/EX2: J5.17, R724.2
/EX2_INT: R724.1, U9.15 (P12)
/EX3: J5.18, R725.2
/EX3_INT: R725.1, U9.16 (P13)
/EX4: J5.19, R726.2
/EX4_INT: R726.1, U9.17 (P14)
/EX5: J5.20, R727.2
/EX5_INT: R727.1, U9.18 (P15)
/EX6: J5.21, R728.2
/EX6_INT: R728.1, U9.19 (P16)
/EX7: J5.22, R729.2
/EX7_INT: R729.1, U9.20 (P17)
/FG_ALERT_N: R125.1, U8.5, U9.8 (P04)
/GND: C101.2, C103.2, C104.2, C105.2, C106.2, C107.2, C108.2, C109.2, C110.2, C111.2, C112.2, C114.2, C115.2, C116.2, C117.2, C118.2, C119.2, C120.2, C121.2, C122.2, C123.2, C124.2, C201.2, C202.2, C203.2, C301.2, C302.2, C303.2, C304.2, C305.2, C306.2, C307.2, C308.2, C309.2, C311.2, C312.2, C313.2, C314.2, C315.2, C316.2, C317.2, C401.2, C402.2, C403.2, C404.2, C501.2, C502.2, C503.2, C504.2, C510.2, C511.2, C512.2, C513.2, C515.2, C516.2, C517.2, C601.2, C602.2, C603.2, C604.2, C605.2, C606.2, C607.2, C608.2, C609.2, C617.2, C701.2, C702.2, C703.2, C704.2, C705.2, C706.2, C707.2, D101.2 (A), J1.A1 (GND), J1.A12 (GND), J1.B1 (GND), J1.B12 (GND), J2.6 (VSS), J2.9 (DET_B), J2.SH (SHIELD), J5.2, J5.30, LED1.3 (VSS), LED2.3 (VSS), LED3.3 (VSS), LED4.3 (VSS), Q1.2 (S), Q3.1, Q3.2, Q3.3, R101.2, R102.2, R103.2, R105.2, R107.2, R108.2, R111.2, R112.2, R113.2, R114.2, R115.2, R118.2, R121.2, R122.2, R123.2, R126.2, R127.2, R128.2, R302.2, R503.2, R506.2, R603.2, R735.2, RT701.2, SW1.2, SW2.2, SW3.2, SW4.2, SW5.1 (A), SW6.2, SW7.2, SW8.2, TP104.1, U1.1 (GND), U1.40 (GND), U1.41 (GND), U2.1 (DVSS), U2.3 (TVSS1), U2.7 (TVSS2), U2.11 (AVSS), U2.17 (I1), U2.18 (TESTEN), U2.41 (AVSS), U3.2, U3.7, U3.16, U4.1 (VSS), U4.5 (MODE), U5.8 (VSS), U5.17 (VSS), U6.4, U6.10, U6.15, U7.4, U8.1, U8.4, U8.6, U8.9, U9.2 (A1), U9.3 (A2), U9.12 (GND), U9.21 (A0), U10.1, U10.6, U10.7, U11.3, U11.5, U11.8, U11.9, U12.4 (VSS), U13.1, U13.4, U15.2, U16.2 (GND), U17.2, U18.2 (A1), U18.3 (A2), U18.8 (GND), U19.2 (VN), U20.3 (GND), U21.1, U21.2, U21.4, U21.7, U21.9, U21.10, U21.13, U22.3 (GND), U23.4 (GND), U24.2 (VN), U25.2 (VN), Y301.2, Y301.4, Y501.2; also elsewhere on the board
/GPIO1: J5.3, R710.2
/GPIO1_MCU: R710.1, U1.39 (IO1)
/GPIO2: J5.4, R711.2
/GPIO2_MCU: R711.1, U1.38 (IO2)
/GPIO4: J5.5, R712.2
/GPIO4_MCU: R712.1, U1.4 (IO4)
/GPIO8: J5.6, R713.2
/GPIO8_MCU: R713.1, U1.12 (IO8)
/GPIO38_MCU: R606.1, U1.31 (IO38)
/GPIO40: J5.8, R715.2
/GPIO40_MCU: R715.1, U1.33 (IO40)
/GPIO41: J5.9, R716.2
/GPIO41_MCU: R716.1, U1.34 (IO41)
/GPIO42: J5.10, R717.2
/GPIO42_MCU: R717.1, U1.35 (IO42)
/GPIO43: J5.11, R718.2
/GPIO43_MCU: R718.1, U1.37 (TXD0)
/GPIO44: J5.12, R719.2
/GPIO44_MCU: R719.1, U1.36 (RXD0)
/GPIO47: J5.13, R720.2
/GPIO47_MCU: R720.1, U1.24 (IO47)
/GPIO48: J5.14, R721.2
/GPIO48_MCU: R721.1, U1.25 (IO48)
/I2C_SCL: R702.1, R731.1, U1.6 (IO6), U2.27 (NSS/P50_SCL/HSU_RX), U8.7, U9.22 (SCL), U10.13, U11.2, U12.6 (SCL), U18.14 (SCL), U23.6 (SCL); also elsewhere on the board
/I2C_SCL_HDR: J5.24, R731.2, U24.3 (IO2)
/I2C_SDA: R701.1, R730.1, U1.5 (IO5), U2.28 (MOSI/SDA/HSU_TX), U8.8, U9.23 (SDA), U10.14, U11.4, U12.5 (SDA), U18.15 (SDA), U23.5 (SDA); also elsewhere on the board
/I2C_SDA_HDR: J5.23, R730.2, U24.1 (IO1)
/IOEXP_INT_N: R703.1, U1.32 (IO39), U9.1 (~INT), U18.13 (~INT)
/IR_GATE: Q1.1 (G), R602.2, R603.1
/IR_LED_A1: D1.2 (A), R601.2
/IR_LED_A2: D2.2 (A), R610.2
/IR_LED_A3: D3.2 (A), R611.2
/IR_LED_K: D1.1 (K), D2.1 (K), D3.1 (K), Q1.3 (D)
/IR_RX: U1.30 (IO37), U13.3
/IR_RX_VS: C601.1, C602.1, R604.2, U13.2
/IR_TX: R602.1, U1.29 (IO36)
/JTAG_STRAP_TP: TP201.1, U1.15 (IO3)
/LF_5V: C501.1, C502.1, C513.1, C515.1, R501.2, U4.3 (VDD), U17.6, U21.14, Y501.1, Y501.4
/LF_ANT_A: C505.2, J3.1, R503.1
/LF_ANT_B: J3.2, R502.1
/LF_CEXT: C503.1, U4.12 (CEXT)
/LF_CLK_4M: U4.6 (XTAL1), Y501.3
/LF_DIN_5V: U4.9 (DIN), U21.11
/LF_DOUT_5V: U4.10 (DOUT), U22.2
/LF_QGND: C504.1, C509.2, U4.13 (QGND)
/LF_QOD: R501.1, U17.5
/LF_RFID_EN: R506.1, U17.3, U18.9 (P4), U22.1
/LF_RX: C509.1, R504.2, U4.14 (RX)
/LF_SCLK_5V: U4.8 (SCLK), U21.6
/LF_TAP: C506.1, C507.1, C508.1, R502.2, R504.1, TP502.1
/LF_TX1: C505.1, U4.4 (TX1)
/LF_TX2: C506.2, C507.2, C508.2, U4.2 (TX2)
/NFC_DVDD: C302.1, C304.1, C313.1, C314.1, C315.1, R301.2, U2.5 (TVDD), U2.8 (AVDD), U2.39 (DVDD)
/NFC_I0: R301.1, U2.16 (I0)
/NFC_IRQ_N: U1.7 (IO7), U2.25 (P70_IRQ)
/NFC_LOADMOD: TP301.1, U2.2 (LOADMOD)
/NFC_LOOP_A: AE1.1, C310.1, C311.1, R303.2, R305.1
/NFC_LOOP_B: AE1.2, C310.2, C312.1, R304.2
/NFC_OSCIN: C306.1, U2.14 (OSCIN), Y301.1
/NFC_OSCOUT: C307.1, U2.15 (OSCOUT), Y301.3
/NFC_RESET_N: R302.1, U2.38 (~RSTPD), U18.7 (P3)
/NFC_RX: C318.2, R306.2, U2.10 (RX)
/NFC_RX_AC: C318.1, R305.2
/NFC_SVDD: C305.1, U2.37 (SVDD)
/NFC_TX1: L301.1, U2.4 (TX1)
/NFC_TX1_F: C308.1, L301.2, R303.1
/NFC_TX2: L302.1, U2.6 (TX2)
/NFC_TX2_F: C309.1, L302.2, R304.1
/NFC_VMID: C301.1, R306.1, U2.9 (VMID)
/PAIR_N: R509.1, R606.2, SW6.1
/PWR_3V3_PG: R119.1, U6.2
/PWR_SW_ON: R116.2, SW5.3 (C)
/RGB_BUF_5V: R605.1, U20.4
/RGB_D1_2: LED1.2 (DOUT), LED2.4 (DIN)
/RGB_D2_3: LED2.2 (DOUT), LED3.4 (DIN)
/RGB_D3_4: LED3.2 (DOUT), LED4.4 (DIN)
/RGB_DATA: U1.18 (IO10), U20.2
/RGB_DIN1: LED1.4 (DIN), R605.2
/RTC_OSCI: U12.1 (OSCI), Y701.1
/RTC_OSCO: U12.2 (OSCO), Y701.2
/SD_CS_DEV: J2.2 (DAT3/CD), R510.2, R515.1, U19.1 (IO1)
/SD_CS_N: R510.1, U1.10 (IO17)
/SD_DAT1: J2.8 (DAT1), R518.1
/SD_DAT2: J2.1 (DAT2), R514.1
/SD_DETECT_N: J2.10 (DET_A), R519.1, U9.4 (P00)
/SD_MISO: J2.7 (DAT0), R513.2, R517.1, U19.6 (IO4)
/SD_MOSI: J2.3 (CMD), R511.2, R516.1, U19.3 (IO2)
/SD_SCK: J2.5 (CLK), R512.2, U19.4 (IO3)
/SPI_MISO: R403.1, R513.1, R734.1, U1.21 (IO13), U22.4
/SPI_MISO_HDR: J5.27, R734.2, U25.1 (IO1)
/SPI_MOSI: R129.2, R511.1, R733.1, U1.19 (IO11), U21.12
/SPI_MOSI_HDR: J5.26, R733.2, U25.3 (IO2)
/SPI_MOSI_JMP: R129.1, R402.1
/SPI_SCK: R401.1, R512.1, R732.1, U1.20 (IO12), U21.5
/SPI_SCK_HDR: J5.25, R732.2, U25.4 (IO3)
/STRAP_BOOT_TP: TP202.1, U1.16 (IO46)
/STRAP_VDD_SPI_TP: TP203.1, U1.26 (IO45)
/SUBGHZ_CS_N: R404.1, U1.22 (IO14)
/SUBGHZ_GDO0: U1.8 (IO15), U3.18
/SUBGHZ_GDO2: U1.9 (IO16), U3.20
/SUBGHZ_RF_ANT: A1.1, C404.1, R405.2
/SUBGHZ_RF_MOD: C403.1, R405.1, U3.6
/SUB_CS_N: R404.2, R406.1, U3.14
/SUB_MISO: R403.2, U3.12
/SUB_MOSI: R402.2, U3.13
/SUB_SCK: R401.2, U3.15
/U6_FB: R117.2, R118.1, U6.5
/U6_L1: L6.1, U6.11
/U6_L2: L6.2, U6.9
/U6_PS_SYNC: R735.1, SW5.2 (B), U6.1, U6.14
/U6_VAUX: C107.1, U6.3
/U7_FB: C113.2, R120.2, R121.1, U7.1
/U7_SW: L7.2, U7.5
/U15_ILIM: R123.1, U15.5
/USB_CC1: J1.A5 (CC1), R101.1, U16.4 (I/O3)
/USB_CC2: J1.B5 (CC2), R102.1, U16.6 (I/O4)
/USB_CONN_N: J1.A7 (D-), J1.B7 (D-), R201.1, U16.3 (I/O2)
/USB_CONN_P: J1.A6 (D+), J1.B6 (D+), R202.1, U16.1 (I/O1)
/USB_D_N: R201.2, U1.13 (USB_D-)
/USB_D_P: R202.2, U1.14 (USB_D+)
/USB_SHIELD: C101.1, J1.SH (SHIELD), R103.1
/USER_BUTTON_A_N: R608.1, SW3.1, U18.11 (P6)
/USER_BUTTON_B_N: R609.1, SW4.1, U18.12 (P7)
/USER_BUTTON_SELECT_N: R607.1, SW7.1, U9.11 (P07)
/VBUS_FUSED: C103.1, C106.1, D101.1 (K), F1.2, TP106.1, U5.13 (IN), U16.5 (VBUS)
/VBUS_USB: F1.1, J1.A4 (VBUS), J1.A9 (VBUS), J1.B4 (VBUS), J1.B9 (VBUS), TP105.1
/VSYS: C105.1, C108.1, C109.1, C114.1, C122.1, C123.1, L7.1, R116.1, TP107.1, U5.10 (OUT), U5.11 (OUT), U6.12, U6.13, U7.3
unnamed: SW8.1, U1.23 (IO21)

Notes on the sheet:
01 USB / BATTERY / POWER
02 ESP32-S3 MCU / USB
03 PN532 NFC / TUNABLE LOOP
04 E07 CC1101 SUB-GHZ
05 LF RFID / SECURITY / MICROSD
06 IR / RGB / BUTTONS
07 SENSORS / RTC / IO EXPANSION

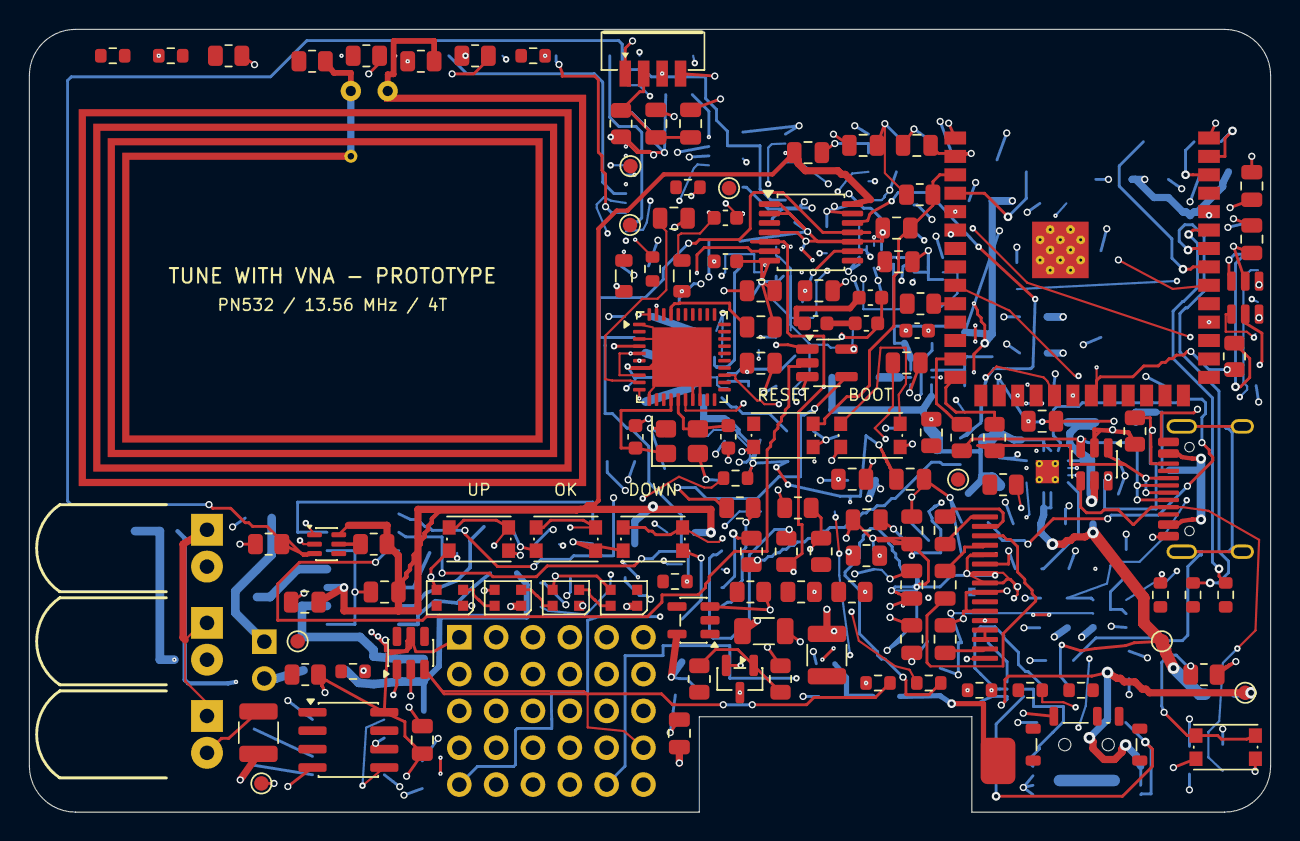
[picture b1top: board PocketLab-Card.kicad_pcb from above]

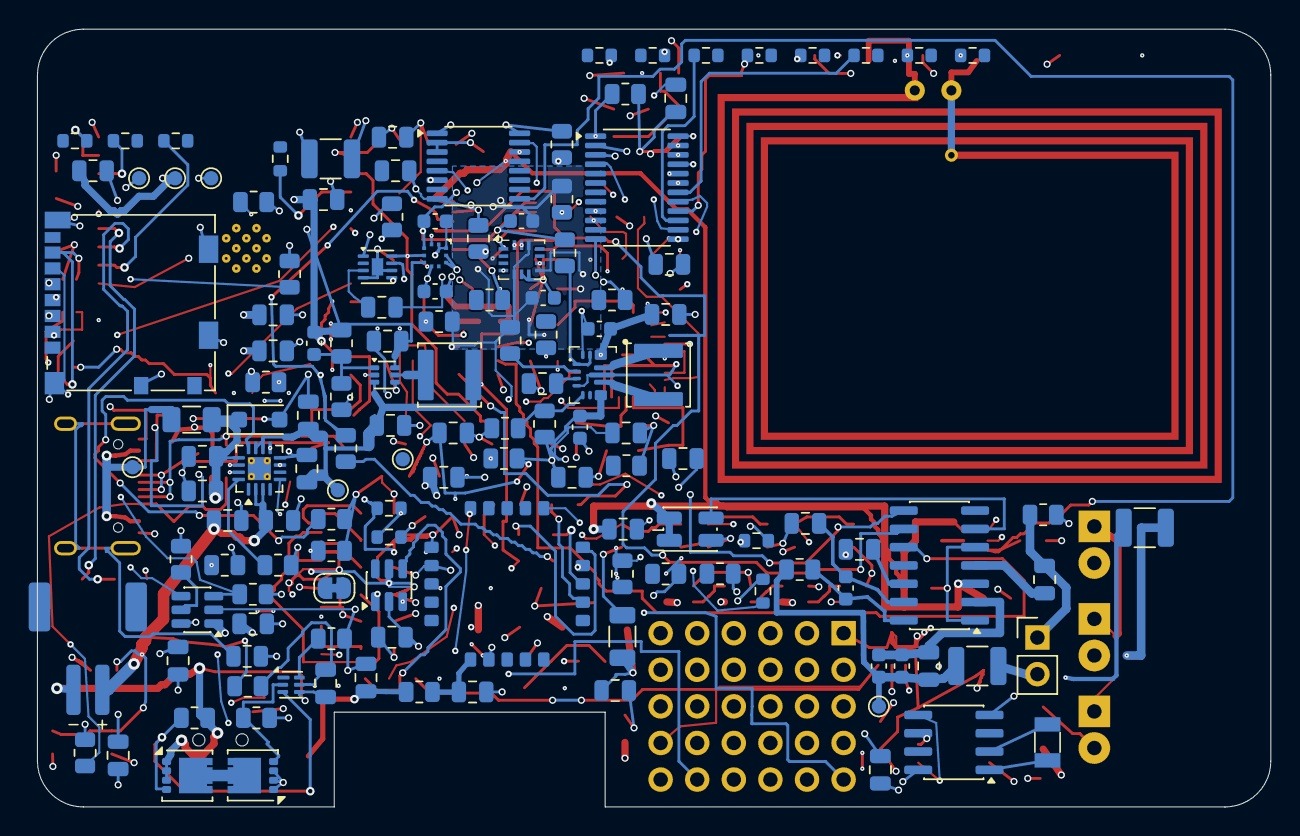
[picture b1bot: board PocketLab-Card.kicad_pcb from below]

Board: 4 copper layers, 85.6 x 54.0 mm, 267 parts (140 on the bottom side), 181 nets.

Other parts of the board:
C610, C611: 1uF X7R; C_0805_2012Metric
C612, C616: 100nF X7R; C_0805_2012Metric
C613, C615: 4.7uF X5R; C_0805_2012Metric
C614: 2.2uF X7R; C_0805_2012Metric
J8: ER-OLED0.42-1W 72x40 SSD1306B; EastRising_ER-OLED0.42-1W_SolderFPC

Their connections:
/+3V3: C612.1, C613.1, J8.5, J8.7, J8.8; also elsewhere on the board
/ESP_EN: J8.10; also elsewhere on the board
/GND: C612.2, C613.2, C614.2, C615.2, C616.2, J8.6, J8.9, J8.11; also elsewhere on the board
/I2C_SCL: J8.12; also elsewhere on the board
/I2C_SDA: J8.13, J8.14; also elsewhere on the board
/OLED_C1N: C611.2, J8.4
/OLED_C1P: C611.1, J8.3
/OLED_C2N: C610.2, J8.2
/OLED_C2P: C610.1, J8.1
/OLED_VCC: C615.1, C616.1, J8.16
/OLED_VCOMH: C614.1, J8.15

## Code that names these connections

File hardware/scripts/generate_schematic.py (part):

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    b = "02 ESP32-S3 MCU / USB"
    add(b, "RF_Module:ESP32-S3-WROOM-1", "U1", "ESP32-S3-WROOM-1-N8R2",
        "PocketLab_Card:ESP32-S3-WROOM-1_PhysicalCourtyard", 355.6, 114.3,
        {"1": "GND", "2": "+3V3", "3": "ESP_EN", "4": "GPIO4_MCU", "5": "I2C_SDA",
         "6": "I2C_SCL", "7": "NFC_IRQ_N", "8": "SUBGHZ_GDO0", "9": "SUBGHZ_GDO2",
         "10": "SD_CS_N", "11": NC, "12": "GPIO8_MCU", "13": "USB_D_N",
         "14": "USB_D_P", "15": "JTAG_STRAP_TP", "16": "STRAP_BOOT_TP", "17": "BOARD_TEMP_ADC",
         "18": "RGB_DATA", "19": "SPI_MOSI", "20": "SPI_SCK", "21": "SPI_MISO",
         "22": "SUBGHZ_CS_N", "23": "USER_BUTTON_AUX_N", "24": "GPIO47_MCU",
         "25": "GPIO48_MCU", "26": "STRAP_VDD_SPI_TP", "27": "BOOT_N",
         "28": NC, "29": "IR_TX", "30": "IR_RX", "31": "GPIO38_MCU",
         "32": "IOEXP_INT_N", "33": "GPIO40_MCU", "34": "GPIO41_MCU", "35": "GPIO42_MCU",
         "36": "GPIO44_MCU", "37": "GPIO43_MCU", "38": "GPIO2_MCU", "39": "GPIO1_MCU",
         "40": "GND", "41": "GND"}, Manufacturer="Espressif", MPN="ESP32-S3-WROOM-1-N8R2", LCSC="C2913204")
    passive(b, "R201", "22R", R0805, 317.5, 177.8, "USB_CONN_N", "USB_D_N")
    passive(b, "R202", "22R", R0805, 330.2, 177.8, "USB_CONN_P", "USB_D_P")
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    # pad.  This removes the former module's undimensioned I-PEX position and
    # lets the board carry a short, controlled feed to the edge antenna.
    pinmap = {str(i): NC for i in (3, 4, 5, 8, 9, 10, 11, 17, 19)}
    pinmap.update({"1": "+3V3", "2": "GND", "6": "SUBGHZ_RF_MOD", "7": "GND",
                   "12": "SUB_MISO", "13": "SUB_MOSI", "14": "SUB_CS_N",
                   "15": "SUB_SCK", "16": "GND", "18": "SUBGHZ_GDO0",
                   "20": "SUBGHZ_GDO2"})
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        passive(b, f"C{602 + index}", "100nF", C0805, x, 482.6, "+5V_RAW", "GND")
    passive(b, "R605", "68R", R0603, 63.5, 457.2, "RGB_BUF_5V", "RGB_DIN1")
    passive(b, "R606", "100R PAIR GPIO PROTECTION", R0603, 127.0, 520.7,
            "GPIO38_MCU", "PAIR_N")
    # Three compact, identical UI buttons provide deterministic UP/DOWN/OK
    # navigation without borrowing RESET, BOOT or the security PAIR button.
    # SELECT uses the former optional BMP390 interrupt input on U9; pressure
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
    direct = [1, 2, 4, 8, 9, 40, 41, 42, 43, 44, 47, 48]
    for offset, gpio in enumerate(direct):
        internal_net = "BOARD_TEMP_ADC" if gpio == 9 else f"GPIO{gpio}_MCU"
        header_net = "BOARD_TEMP_HDR" if gpio == 9 else f"GPIO{gpio}"
        value = "100R BOARD TEMP PROBE" if gpio == 9 else "100R"
        passive(b, f"R{710 + offset}", value, R0603,
                317.5 + (offset % 6) * 25.4, 546.1 + (offset // 6) * 25.4,
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        Manufacturer="onsemi", MPN="SRV05-4MR6T1G", LCSC="C604719")

    header = {
        "1": "+3V3", "2": "GND", "3": "GPIO1", "4": "GPIO2", "5": "GPIO4", "6": "GPIO8",
        "7": "BOARD_TEMP_HDR", "8": "GPIO40", "9": "GPIO41", "10": "GPIO42", "11": "GPIO43",
        "12": "GPIO44", "13": "GPIO47", "14": "GPIO48", "15": "EX0", "16": "EX1",
        "17": "EX2", "18": "EX3", "19": "EX4", "20": "EX5", "21": "EX6", "22": "EX7",
        "23": "I2C_SDA_HDR", "24": "I2C_SCL_HDR", "25": "SPI_SCK_HDR", "26": "SPI_MOSI_HDR",
        "27": "SPI_MISO_HDR", "28": "CHG_TS", "29": "+5V_AUX", "30": "GND",
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
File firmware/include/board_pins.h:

#pragma once

#include <stdint.h>

namespace pocketlab::pins {

// Boot and shared buses
inline constexpr uint8_t BOOT_N = 0;
inline constexpr uint8_t I2C_SDA = 5;
inline constexpr uint8_t I2C_SCL = 6;
inline constexpr uint8_t SPI_MOSI = 11;
inline constexpr uint8_t SPI_SCK = 12;
inline constexpr uint8_t SPI_MISO = 13;

// NFC
inline constexpr uint8_t NFC_IRQ_N = 7;

// LEDs
inline constexpr uint8_t RGB_DATA = 10;

// Sub-GHz
inline constexpr uint8_t SUBGHZ_CS_N = 14;
inline constexpr uint8_t SUBGHZ_GDO0 = 15;
inline constexpr uint8_t SUBGHZ_GDO2 = 16;

// Storage
inline constexpr uint8_t SD_CS_N = 17;

// 125-kHz LF RFID (HTRC110 through 3.3-V/5-V level translators)
inline constexpr uint8_t LF_SCLK = 18;
inline constexpr uint8_t LF_DOUT = 21;
inline constexpr uint8_t LF_DIN = 35;

// Dedicated physical app-pairing button
inline constexpr uint8_t PAIR_N = 38;

// Native USB
inline constexpr uint8_t USB_D_N = 19;
inline constexpr uint8_t USB_D_P = 20;

// I/O expander interrupt
inline constexpr uint8_t IOEXP_INT_N = 39;

// Infrared
inline constexpr uint8_t IR_TX = 36;
inline constexpr uint8_t IR_RX = 37;

// Internal 10-k NTC divider. J5 pin 7 is only a protected, high-impedance
// probe point for this node; GPIO9 must never be driven.
inline constexpr uint8_t BOARD_TEMP_ADC = 9;

// Direct expansion GPIOs
inline constexpr uint8_t DIRECT_EXPANSION[] = {
    1, 2, 4, 8, 40, 41, 42, 43, 44, 47, 48,
};

// U9 / TCA9535 at 0x20. Both ports remain inputs; P10-P17 are EX0-EX7.
enum class StatusExpanderPin : uint8_t {
  SdDetectN = 0,
  ChargerN = 1,
  ChargerPowerGoodN = 2,
  Aux5FaultN = 3,
  FuelGaugeAlertN = 4,
  BmiInt1 = 5,
  BmiInt2 = 6,
  BmpInt = 7,
  Ex0 = 8,
  Ex1 = 9,
  Ex2 = 10,
  Ex3 = 11,
  Ex4 = 12,
  Ex5 = 13,
  Ex6 = 14,
  Ex7 = 15,
};

// U18 / TCA9534 at 0x21. P0-P5 are outputs and P6-P7 are inputs.
enum class ControlExpanderPin : uint8_t {
  ChargerUsbModeEn1 = 0,
  ChargerDisable = 1,
  Aux5Enable = 2,
  NfcResetN = 3,
  LfRfidPowerEnable = 4,
  Boost5Enable = 5,
  UserButtonAN = 6,
  UserButtonBN = 7,
};

}  // namespace pocketlab::pins
